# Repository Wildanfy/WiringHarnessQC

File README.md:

**README.md**

---

## QC Cable Tester Berbasis ESP32 + Bluetooth

**Deskripsi Singkat**
Proyek ini adalah implementasi sistem Quality Control (QC) untuk pengujian konektivitas kabel, menggunakan modul ESP32, rangkaian shift register 80/88-bit, multiplexer (MUX) hingga 6 buah, dan koneksi Bluetooth. Dengan satu rangkaian, Anda dapat memeriksa hingga 76 kanal “normal” dan 8 kanal “X” secara otomatis. Hasil QC (terhubung, putus, short, salah jalur) kemudian dikirim melalui USB Serial dan Bluetooth Serial secara bersamaan dalam format teks.

---

## Daftar Isi

1. [Fitur Utama](#fitur-utama)
2. [Persyaratan Hardware](#persyaratan-hardware)
3. [Skema Pin dan Konektivitas](#skema-pin-dan-konektivitas)
4. [Persiapan Perangkat Lunak](#persiapan-perangkat-lunak)
5. [Cara Mengunggah (Upload) ke ESP32](#cara-mengunggah-upload-ke-esp32)
6. [Perintah Bluetooth / USB Serial](#perintah-bluetooth--usb-serial)
7. [Penjelasan Fungsi-Fungsi Utama](#penjelasan-fungsi-fungsi-utama)
8. [Format Output QC](#format-output-qc)

---

## Fitur Utama

* **Pengujian 76 Kanal Normal**

  * Memanfaatkan 5 buah MUX 16:1 untuk membaca kondisi setiap pin kabel di kanal 1–76.
  * Deteksi otomatis:

    * `C` (Connected)
    * `N` (Disconnected)
    * `S&<nomor partner>` (Short dengan kanal lain)
    * `W&<nomor partner>` (Miswire / salah jalur)
  * Penanganan kondisi khusus (edge-case) pada grup K2 dan K3 sesuai skema QC kabel di dokumentasi.
* **Pengujian 8 Kanal “X” (MUX6)**

  * Rangkaian tambahan untuk kabel tipe “X” (kanal 80–87) menggunakan MUX6.
  * Deteksi antar-MUX: apabila kanal X terhubung / short / miswire ke salah satu dari 88 global bit (76 kanal normal + 8 X).
* **Bluetooth Serial + USB Serial**

  * Nama perangkat Bluetooth: **“QC Cable”**
  * Hasil pengukuran QC langsung dikirim ke kedua antarmuka (Serial USB & Bluetooth).
  * Komunikasi satu arah (ESP32 → PC / Handphone) untuk log hasil QC.
* **Mode QC Fleksibel**

  * `start` : hanya QC kabel normal (1–76)
  * `startx`: hanya QC kabel X (80–87)
  * `startall`: QC semua secara bersamaan (1–76 dan 80–87)
  * `stop` : menghentikan pengukuran QC dan mereset pin

---

## Persyaratan Hardware

1. **ESP32** (atau varian serupa dengan fitur BluetoothClassic)
2. **Shift Register 80-bit / 88-bit**

   * Anda dapat menyusun rangkaian shift register (misalnya menggunakan beberapa IC 74HC595 beruntun) untuk total 80 bit.
   * Untuk skema kabel “X” (8 kanal tambahan), gunakan shift register hingga 88 bit.
3. **Multiplexer (MUX)**

   * 5 buah MUX 16:1 (misal CD74HC4067 atau sejenis). Masing-masing MUX menangani 16 bit sinyal dari shift register untuk 76 kanal normal (5×16 = 80, gunakan 76).
   * 1 buah MUX 16:1 untuk kabel “X” (kanal 80–87).
4. **Kabel Jumper / Breadboard**
5. **Catu Daya 5V (untuk MUX & Shift Register)**
6. **Kabel Uji / Fixture**

   * Sambungkan kabel-kabel yang akan diuji ke pin output shift register / MUX sesuai diagram.
7. **Komputer / Smartphone**

   * Untuk menerima data QC via USB Serial atau Bluetooth Serial.

---

## Skema Pin dan Konektivitas

```
ESP32                              Shift Register / MUX / Fixture
--------------------------------------------------------------------------------
GPIO 23   (DS)      → Data (SER) pada shift register
GPIO 18   (SHCP)    → Clock (SRCLK) pada shift register
GPIO 5    (STCP)    → Latch (RCLK) pada shift register

GPIO 26   (SIG)     ← Output “sense” (hasil pembacaan) dari MUX (digitalRead)
GPIO 13   (S0)      → Select bit 0 pada semua MUX (S0)
GPIO 12   (S1)      → Select bit 1 pada semua MUX (S1)
GPIO 14   (S2)      → Select bit 2 pada semua MUX (S2)
GPIO 19   (S3)      → Select bit 3 pada semua MUX (S3)

GPIO 25   (EN_MUX1) → Enable MUX1 (untuk kanal 1–16)
GPIO 33   (EN_MUX2) → Enable MUX2 (untuk kanal 17–32)
GPIO 15   (EN_MUX3) → Enable MUX3 (untuk kanal 33–48)
GPIO 2    (EN_MUX4) → Enable MUX4 (untuk kanal 49–64)
GPIO 4    (EN_MUX5) → Enable MUX5 (untuk kanal 65–80)

GPIO 27   (EN_MUX6) → Enable MUX6 (untuk kabel X, kanal 80–87)
```

* **Catatan Channel Mapping**

  * Kanall 1–13 → `K1-A1` … `K1-A13`
  * Kanall 14–26 → `K1-B1` … `K1-B13`
  * Kanall 27–39 → `K2-A1` … `K2-A13`
  * Kanall 40–52 → `K2-B1` … `K2-B13`
  * Kanall 53–64 → `K3-A1` … `K3-A12`
  * Kanall 65–76 → `K3-B1` … `K3-B12`
  * Kabel “X” (8 kanal) → `X-1` … `X-8`

---

## Persiapan Perangkat Lunak

1. **Install Arduino IDE (versi terbaru disarankan)**

   * Bisa diunduh di [https://www.arduino.cc/en/software](https://www.arduino.cc/en/software) (sesuaikan OS)
2. **Tambahkan Board ESP32 ke Arduino IDE**

   * Buka **File → Preferences**
   * Tambahkan URL berikut ke `Additional Boards Manager URLs`:

     ```
     https://raw.githubusercontent.com/espressif/arduino-esp32/gh-pages/package_esp32_index.json
     ```
   * Buka **Tools → Board → Boards Manager**, cari “esp32” lalu install “esp32 by Espressif Systems”.
3. **Library yang Diperlukan**

   * `BluetoothSerial.h` (sudah tersedia saat menginstal board ESP32)
   * Tidak ada library eksternal lain (semua fungsi shift register dan multiplexer ditulis manual).

---

## Cara Mengunggah (Upload) ke ESP32

1. Sambungkan ESP32 ke komputer via kabel USB.
2. Pastikan di **Tools → Board** sudah terbaca **“ESP32 Dev Module”** (atau tipe ESP32 yang Anda gunakan).
3. Pilih **Port** yang sesuai (Tools → Port).
4. Buka file `QC_Cable.ino` (atau ganti nama menjadi `QC_Cable.ino`) pada Arduino IDE.
5. Tekan tombol **Upload** (ikon panah kanan). Tunggu hingga proses selesai, ESP32 otomatis restart.

---

## Perintah Bluetooth / USB Serial

Setelah kode berhasil berjalan, ESP32 akan menunggu perintah via USB Serial (baud rate 115200) ataupun Bluetooth Serial (“QC Cable”).
Ketik salah satu perintah berikut (tanpa tanda kutip) lalu tekan **Enter**:

* `start`

  * Menjalankan QC hanya untuk **kanal normal** (1–76).
* `startx`

  * Menjalankan QC hanya untuk **kanal “X”** (80–87).
* `startall`

  * Menjalankan QC untuk **semua kanal** (1–76 dan 80–87).
* `stop`

  * Menghentikan QC, mereset pin, dan berhenti mengirim data.

**Contoh penggunaan di Serial Monitor:**

```
> startall
```

ESP32 akan mengirimkan hasil QC berulang setiap interval 10 ms ke Serial/BT.

---

## Penjelasan Fungsi-Fungsi Utama

1. **`resetPins()`**

   * Mengatur semua pin ESP32 (DS, SHCP, STCP, SIG, S0–S3, EN\_MUX1–EN\_MUX6) ke `OUTPUT` atau `INPUT_PULLDOWN` sesuai fungsinya.
   * Memastikan initial state: latch low, clock low, data low, MUX6 (EN\_MUX6) di-`HIGH` (non-aktif).

2. **`shiftOut80(uint64_t data)`**

   * Mengirim 76 bit (dipadatkan menjadi 80 bit) ke rangkaian shift register secara paling signifikan (MSB) terlebih dahulu.
   * `data` berupa `uint64_t` dimana bit ke-0 (LSB) → kanal terakhir (nomor 75).

3. **`readMux16(int muxNumber)`**

   * Membaca 16 bit data dari MUX tertentu (1–5) dengan mengaktifkan satu `EN_MUXx` pada `LOW` dan membaca pin SIG pada setiap kombinasi `S0–S3`.
   * Mengembalikan `uint16_t` yang menandakan status HIGH/LOW pada 16 output MUX.

4. **`readAllMux(bool globalMap[], int maxCh)`**

   * Membaca MUX1–5 sekaligus, memasukkan hasilnya ke array `globalMap[]` (panjang minimal `maxCh`).
   * Hanya mengisi hingga indeks `maxCh−1`.

5. **`runQC_K1(String &outputBuffer)`**, **`runQC_K2(...)`**, **`runQC_K3(...)`**

   * Masing-masing menangani QC pada grup kabel:

     * **K1** = kanal global 0–25 (K1-A1..K1-A13, K1-B1..K1-B13)
     * **K2** = kanal global 26–51 (K2-A1..K2-A13, K2-B1..K2-B13)
     * **K3** = kanal global 52–75 (K3-A1..K3-A12, K3-B1..K3-B12)
   * Setiap fungsi:

     1. **Inisialisasi** array `ChannelResult results[...]` (state & partner).
     2. Untuk tiap channel `ch` di kelompoknya:

        * Jika `channelUsed[ch]` = `false`, tandai state = −1 (skip).
        * Lakukan `shiftOut80(1ULL << ch)`, delay, `readAllMux(...)` ke `globalMap[]`.
        * Hitung `totalActive` dalam kelompok tersebut.
        * Tentukan `state` (CONNECTED, SHORT, MISWIRE, DISCONNECTED) dan `partner` (jika SHORT/MISWIRE).
        * Penanganan **kondisi khusus**:

          * **K2**

            * Jika B2 (index internal 10) short ke B13 (index internal 25), dan B13 dianggap putus, tandai kedua channel sebagai CONNECTED.
          * **K3**

            * Jika A5 (index internal 4) putus, dan B1 (index internal 12) short ke A5, tandai keduanya sebagai CONNECTED.
     3. **Cetak hasil**: untuk tiap channel, bentuk string `"Label:State,"` (contoh: `K1-A1:C,` atau `K2-B5:W&B12,`). Tambahkan ke `outputBuffer`.

6. **`shiftOut88(uint8_t data[11])`**

   * Serupa `shiftOut80`, tetapi menggunakan array 11 byte untuk total 88 bit (1 bit extra).

7. **`readMux16X()`**

   * Membaca MUX6 (kanal X) dengan mengaktifkan `EN_MUX6 = LOW` dan membaca 16 bit, meski kanal X hanya 8 bit (bit 0–7).

8. **`runQCX(String &outputBuffer)`**

   * Menangani QC untuk 8 kanal X (global bit 80–87).
   * Algoritmanya mirip `runQC_K*`, tetapi mencakup pembacaan **seluruh 88 bit** (MUX1–5 + MUX6) untuk deteksi antar-MUX.
   * Hasil (“X-1\:C,” atau “X-3\:S\&K2-A5,” dst.) ditambahkan ke `outputBuffer`.

9. **`setup()`**

   * Inisialisasi pin dan `Serial.begin(115200)`, `SerialBT.begin("QC Cable")`.
   * `delay(1000)` singkat agar Bluetooth siap.

10. **`loop()`**

    * Terus-menerus:

      * Baca karakter dari `Serial` (USB) & `SerialBT` (Bluetooth), kumpulkan ke `bufUSB` / `bufBT`.
      * Jika ditemukan substring:

        * `"startall"`, `"startx"`, `"start"`, `"stop"` → setel `qcRunning`, `qcActive`, `qcActiveX`, `qcAllActive` sesuai mode.
      * Jika `qcRunning == true` dan interval (10 ms) tercapai:

        * Panggil `runQC_K1()`, `runQC_K2()`, `runQC_K3()` apabila mode `qcActive`/`qcAllActive`.
        * Panggil `runQCX()` apabila mode `qcActiveX`/`qcAllActive`.
        * Kirim `out` (`String` hasil QC) melalui `Serial.println(out)` dan `SerialBT.println(out)`.

---

## Format Output QC

Hasil QC dikomunikasikan dalam satu baris teks, misalnya:

```
K1-A1:C,K1-A2:N,K1-A3:S&K1-B5,...,K3-B12:W&K3-A8,X-1:C,X-2:N,X-3:S&K2-B4,...
```

* **Format umum per-kanal:**

  ```
  <Label>:<State>[&<LabelPartner>],
  ```

  * `<Label>`

    * Contoh: `K1-A1`, `K2-B7`, `K3-A12`, `X-5`
  * `<State>`

    * `C` = Connected (terhubung sempurna satu-ke-satu)
    * `N` = Disconnected (putus, tidak terdeteksi sama sekali)
    * `S&<LabelPartner>` = Short (terhubung dengan lebih dari satu bit; partner ditunjukkan)
    * `W&<LabelPartner>` = Miswire (sinyal keluar dari kelompok yang diharapkan)
  * `<LabelPartner>`

    * Menunjukkan label kanal lain yang terhubung / short / miswire. Pada `S&`/`W&`, `LabelPartner` hanya substring setelah tanda “-” (misal `B5`, `A12`).

**Contoh Lengkap**

```
K1-A1:C,K1-A2:N,K1-A3:S&K1-B5,K1-A4:W&K2-A1,...,K3-B12:C,X-1:N,X-2:C,X-3:S&K1-A7,...
```

---

### Catatan Tambahan

* Pastikan bahwa **`channelUsed[]`** diinisialisasi sesuai kebutuhan. Nilai `false` akan menyebabkan pemrosesan kanal tersebut di-skip. Anda dapat menonaktifkan atau mengaktifkan kanal tertentu dengan mengubah array `channelUsed[76]` pada baris awal kode.
* Jika Anda ingin menyesuaikan interval QC (delay antara iterasi), ubah konstanta `const unsigned long qcInterval = 10;` (nilai dalam milidetik).
* Penanganan edge-case untuk K2 dan K3 ditujukan untuk kondisi khusus kabel tertentu (misal susunan “B2 short ke B13” atau “A5 disconnected & B1 short ke A5”). Silakan sesuaikan logika ini jika topologi kabel Anda berbeda.

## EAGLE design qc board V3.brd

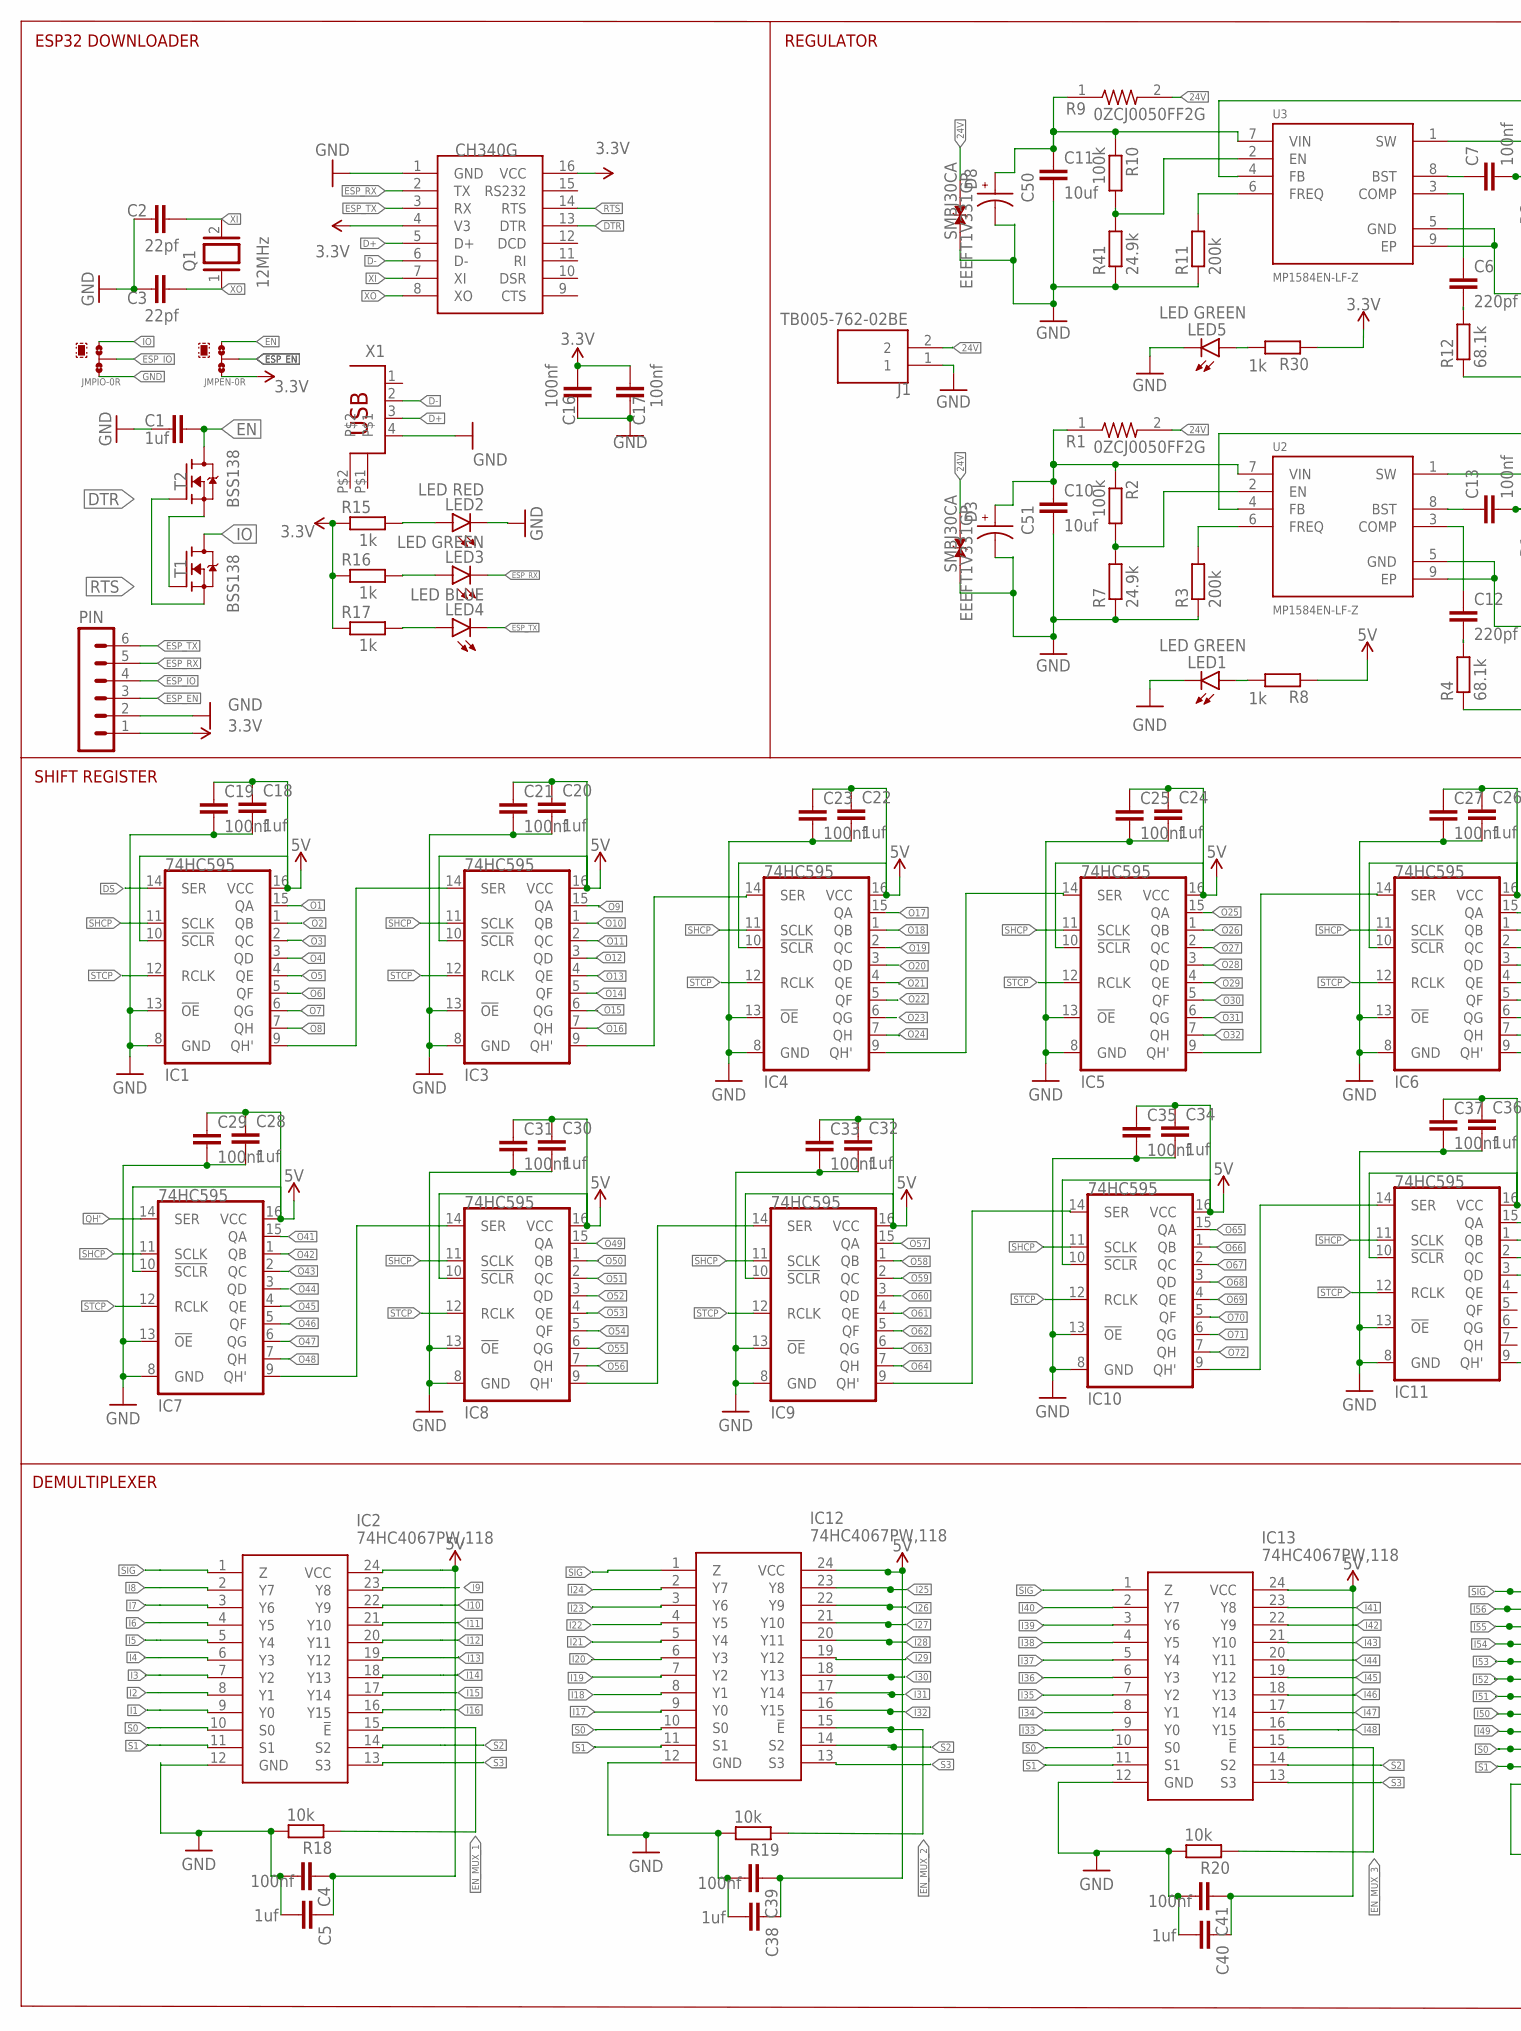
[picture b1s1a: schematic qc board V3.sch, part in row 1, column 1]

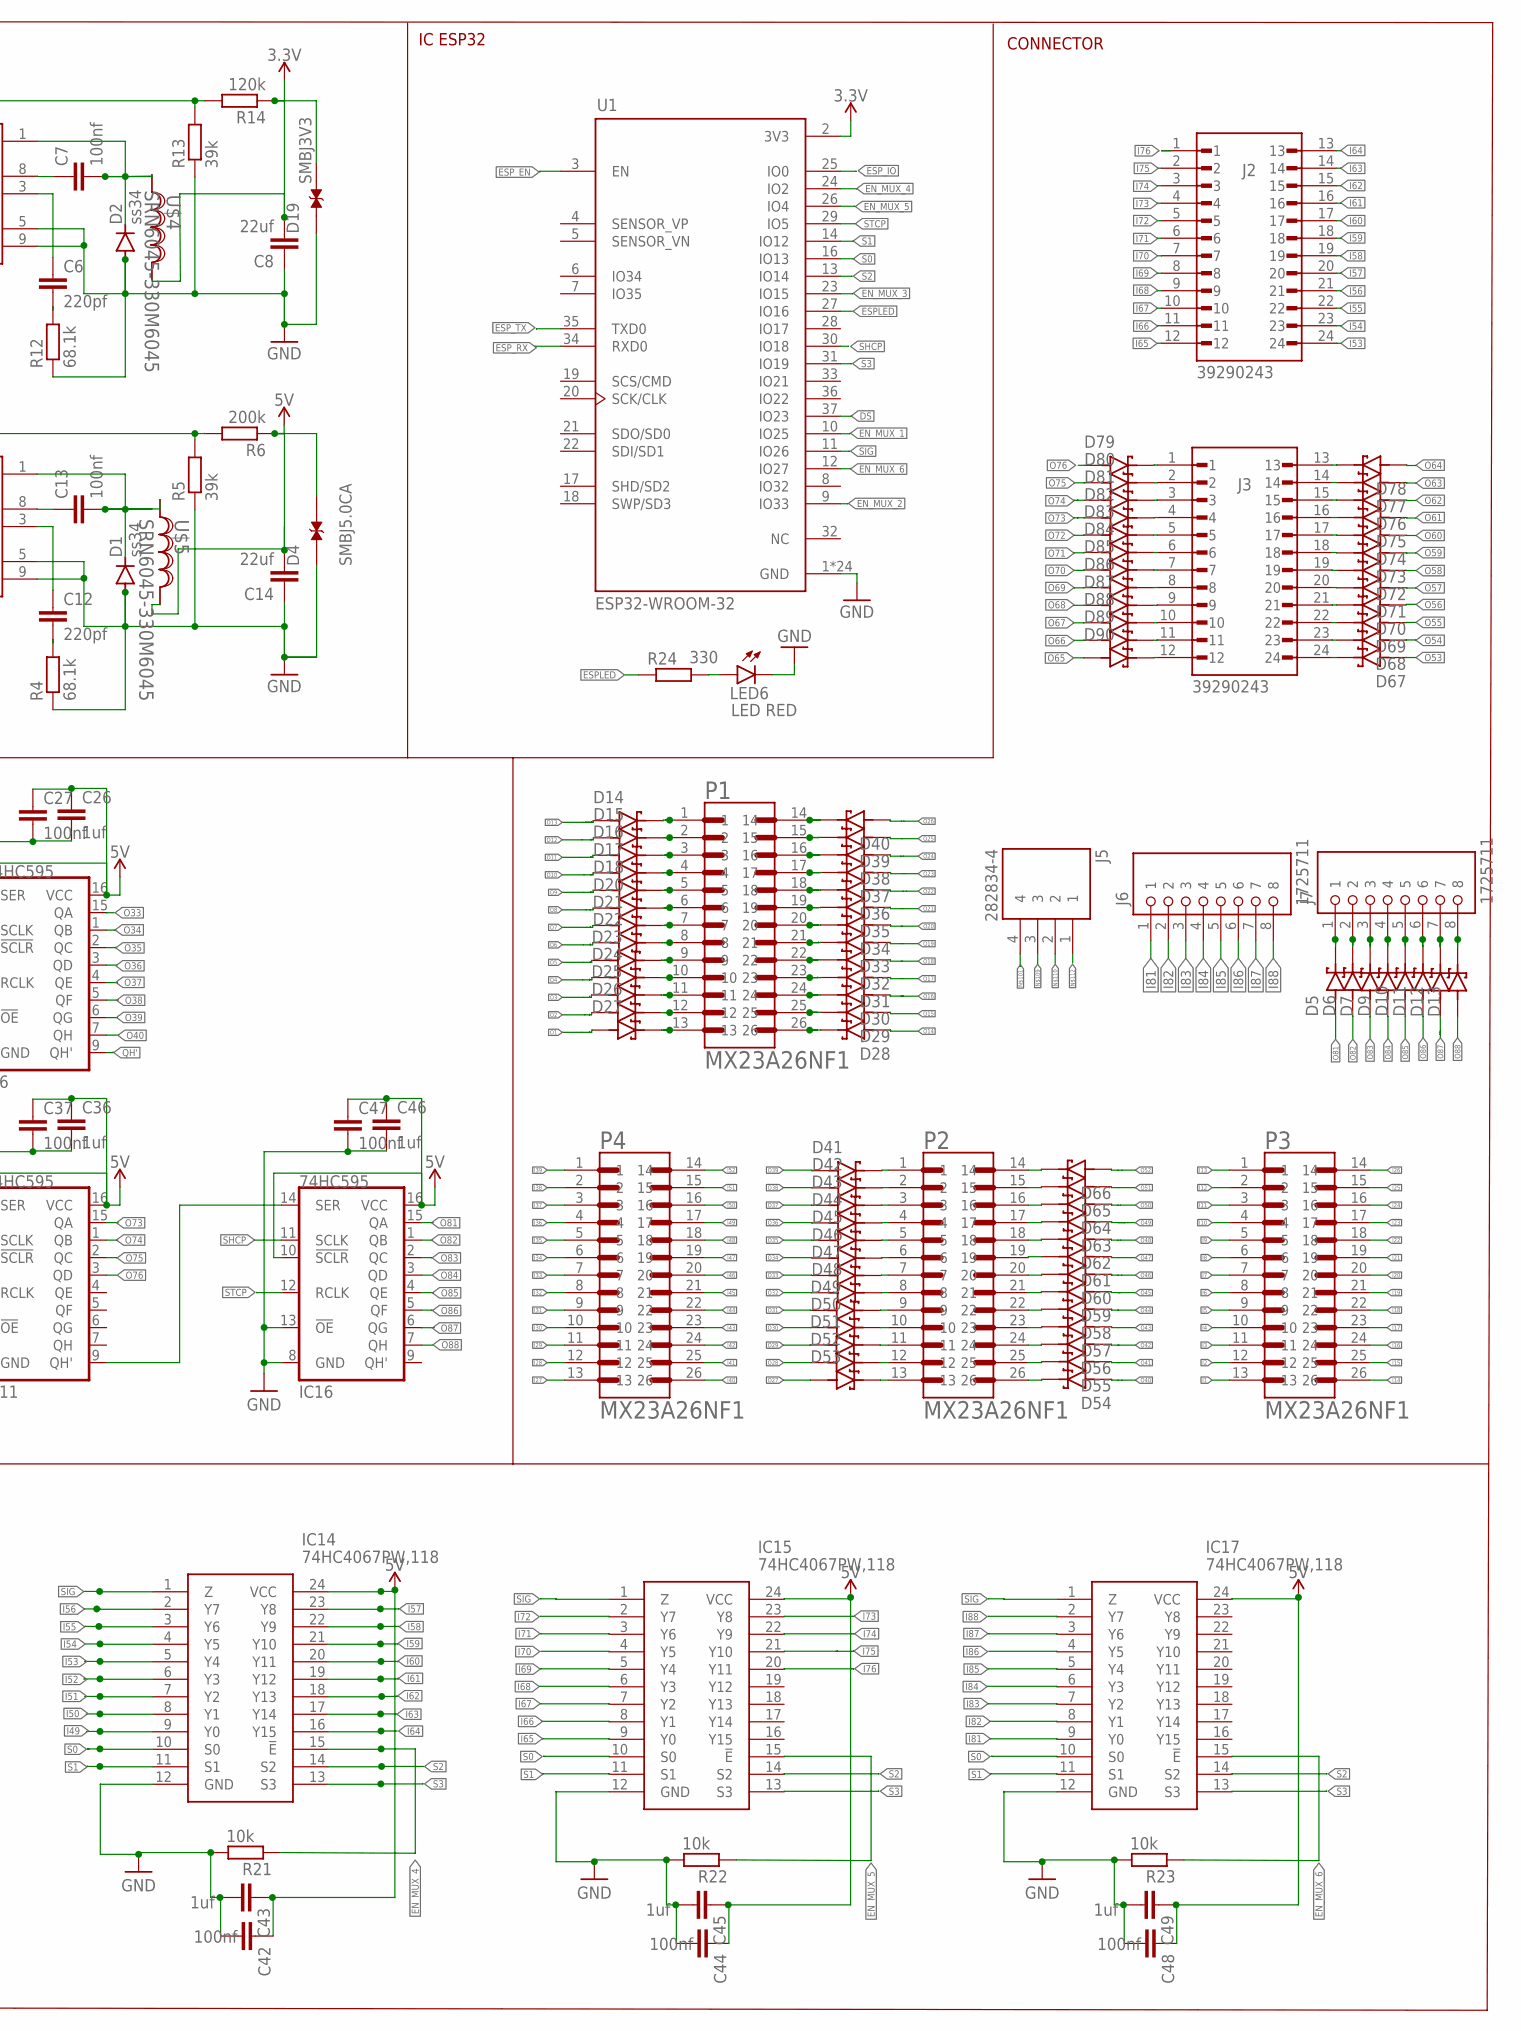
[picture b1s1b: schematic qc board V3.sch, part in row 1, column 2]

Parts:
C1, C5, C18, C20, C22, C24, C26, C28, C30, C32, C34, C36, C38, C40, C43, C45, C46, C49: 1uf; C0805
C2, C3: 22pf; C0805
C4, C7, C13, C16, C17, C19, C21, C23, C25, C27, C29, C31, C33, C35, C37, C39, C41, C42, C44, C47, C48: 100nf; C0805
C6, C12: 220pf; C0805
C8, C14: 22uf; C0805
C10, C11: 10uf; C0805
C50, C51: EEEFT1V331GP; CAP_EEEFT1V331GP
D1, D2: ss34; SMB
D3, D8: SMBJ30CA; DIOM4336X265N
D4: SMBJ5.0CA; DIOM4336X265N
D5, D6, D7, D9, D10, D11, D12, D13, D14, D15, D16, D17, D18, D20, D21, D22, D23, D24, D25, D26, D27, D28, D29, D30, D31, D32, D33, D34, D35, D36, D37, D38, D39, D40, D41, D42, D43, D44, D45, D46, D47, D48, D49, D50, D51, D52, D53, D54, D55, D56, D57, D58, D59, D60, D61, D62, D63, D64, D65, D66, D67, D68, D69, D70, D71, D72, D73, D74, D75, D76, D77, D78, D79, D80, D81, D82, D83, D84, D85, D86, D87, D88, D89, D90: 1N5819HW-7; SOD3715X145N
D19: SMBJ3V3; DIOM4336X265N
IC1, IC3, IC4, IC5, IC6, IC7, IC8, IC9, IC10, IC11, IC16: 74HC595; SO16
IC2, IC12, IC13, IC14, IC15, IC17: 74HC4067PW,118; SOP65P640X110-24N
J1: TB005-762-02BE; CUI_TB005-762-02BE
J2, J3: 39290243; MOLEX_39290243
J5: 282834-4; TE_282834-4
J6, J7: 1725711; PHOENIX_1725711
JMPEN: 0R-JUMPB; B0R-JMP
JMPIO: 0R-JUMPB; B0R-JMP
LED1, LED5: LED GREEN; CHIP-LED0805
LED2: LED RED; CHIPLED_0805
LED3: LED GREEN; CHIPLED_0805
LED4: LED BLUE; CHIPLED_0805
LED6: LED RED; CHIP-LED0805
P1, P2, P3, P4: MX23A26NF1; JAE_MX23A26NF1
PIN: MA06-1
Q1: 12MHz; QS
R1, R9: 0ZCJ0050FF2G; RESC3216X125N
R2, R10: 100k; R0805
R3, R6, R11: 200k; R0805
R4, R12: 68.1k; R0805
R5, R13: 39k; R0805
R7, R41: 24.9k; R0805
R8, R30: 1k; R0805
R14: 120k; R0805
R15, R16, R17: 1k; M0805
R18, R19, R20, R21, R22, R23: 10k; M0805
R24: 330; R0805
T1, T2: BSS138; SOT95P240X111-3N
U1: ESP32-WROOM-32; MODULE_ESP32-WROOM-32
U2, U3: MP1584EN-LF-Z; SOIC127P600X170-9N
U$3: CH340G; SOIC16
U$4, U$5: SRN6045-330M6045; SRN6045
X1: PN61729

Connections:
3.3V: C8.2, C16.1, C17.1, D19.2, JMPEN.3, PIN.1, R14.1, R15.1, R16.1, R17.1, R30.1, U1.2 (3V3), U$3.4 (V3), U$3.16 (VCC), U$4.1
5V: C4.1, C5.1, C14.2, C18.1, C19.1, C20.1, C21.1, C22.1, C23.1, C24.1, C25.1, C26.1, C27.1, C28.1, C29.1, C30.1, C31.1, C32.1, C33.1, C34.1, C35.1, C36.1, C37.1, C38.1, C39.1, C40.1, C41.1, C42.1, C43.1, C44.1, C45.1, C46.1, C47.1, C48.1, C49.1, D4.2, IC1.10 (!SCLR), IC1.16 (VCC), IC2.24 (VCC), IC3.10 (!SCLR), IC3.16 (VCC), IC4.10 (!SCLR), IC4.16 (VCC), IC5.10 (!SCLR), IC5.16 (VCC), IC6.10 (!SCLR), IC6.16 (VCC), IC7.10 (!SCLR), IC7.16 (VCC), IC8.10 (!SCLR), IC8.16 (VCC), IC9.10 (!SCLR), IC9.16 (VCC), IC10.10 (!SCLR), IC10.16 (VCC), IC11.10 (!SCLR), IC11.16 (VCC), IC12.24 (VCC), IC13.24 (VCC), IC14.24 (VCC), IC15.24 (VCC), IC16.10 (!SCLR), IC16.16 (VCC), IC17.24 (VCC), R6.1, R8.1, U$5.1
24V: D3.1, D8.1, J1.2, R1.2, R9.2
D+: U$3.5 (D+), X1.3
D-: U$3.6 (D-), X1.2
DS: IC1.14 (SER), U1.37 (IO23)
DTR: T1.2 (S), T2.1 (G), U$3.13 (DTR)
EN: C1.1, JMPEN.1, T2.3 (D)
EN_MUX_1: IC2.15 (!E), R18.1, U1.10 (IO25)
EN_MUX_2: IC12.15 (!E), R19.1, U1.9 (IO33)
EN_MUX_3: IC13.15 (!E), R20.1, U1.23 (IO15)
EN_MUX_4: IC14.15 (!E), R21.1, U1.24 (IO2)
EN_MUX_5: IC15.15 (!E), R22.1, U1.26 (IO4)
EN_MUX_6: IC17.15 (!E), R23.1, U1.12 (IO27)
ESPLED: R24.1, U1.27 (IO16)
ESP_EN: JMPEN.2, PIN.3, U1.3 (EN)
ESP_IO: JMPIO.2, PIN.4, U1.25 (IO0)
ESP_RX: LED3.C, PIN.5, U1.34 (RXD0), U$3.2 (TX)
ESP_TX: LED4.C, PIN.6, U1.35 (TXD0), U$3.3 (RX)
GND: C1.2, C2.2, C3.2, C4.2, C5.2, C8.1, C10.2, C11.2, C14.1, C16.2, C17.2, C18.2, C19.2, C20.2, C21.2, C22.2, C23.2, C24.2, C25.2, C26.2, C27.2, C28.2, C29.2, C30.2, C31.2, C32.2, C33.2, C34.2, C35.2, C36.2, C37.2, C38.2, C39.2, C40.2, C41.2, C42.2, C43.2, C44.2, C45.2, C46.2, C47.2, C48.2, C49.2, C50.2, C51.2, D1.A, D2.A, D3.2, D4.1, D8.2, D19.1, IC1.8 (GND), IC1.13 (!OE), IC2.12 (GND), IC3.8 (GND), IC3.13 (!OE), IC4.8 (GND), IC4.13 (!OE), IC5.8 (GND), IC5.13 (!OE), IC6.8 (GND), IC6.13 (!OE), IC7.8 (GND), IC7.13 (!OE), IC8.8 (GND), IC8.13 (!OE), IC9.8 (GND), IC9.13 (!OE), IC10.8 (GND), IC10.13 (!OE), IC11.8 (GND), IC11.13 (!OE), IC12.12 (GND), IC13.12 (GND), IC14.12 (GND), IC15.12 (GND), IC16.8 (GND), IC16.13 (!OE), IC17.12 (GND), J1.1, JMPIO.3, LED1.C, LED2.C, LED5.C, LED6.C, PIN.2, R3.1, R4.1, R5.1, R7.1, R11.1, R12.1, R13.1, R18.2, R19.2, R20.2, R21.2, R22.2, R23.2, R41.1, U1.1 (GND), U1.15 (GND), U1.38 (GND), U1.39_1 (GND), U1.39_2 (GND), U1.39_3 (GND), U1.39_4 (GND), U1.39_5 (GND), U1.39_6 (GND), U1.39_7 (GND), U1.39_8 (GND), U1.39_9 (GND), U1.39_10 (GND), U1.39_11 (GND), U1.39_12 (GND), U1.39_13 (GND), U1.39_14 (GND), U1.39_15 (GND), U1.39_16 (GND), U1.39_17 (GND), U1.39_18 (GND), U1.39_19 (GND), U1.39_20 (GND), U1.39_21 (GND), U2.5 (GND), U2.9 (EP), U3.5 (GND), U3.9 (EP), U$3.1 (GND), X1.4
I1: IC2.9 (Y0), P3.13
I2: IC2.8 (Y1), P3.12
I3: IC2.7 (Y2), P3.11
I4: IC2.6 (Y3), P3.10
I5: IC2.5 (Y4), P3.9
I6: IC2.4 (Y5), P3.8
I7: IC2.3 (Y6), P3.7
I8: IC2.2 (Y7), P3.6
I9: IC2.23 (Y8), P3.5
I10: IC2.22 (Y9), P3.4
I11: IC2.21 (Y10), P3.3
I12: IC2.20 (Y11), P3.2
I13: IC2.19 (Y12), P3.1
I14: IC2.18 (Y13), P3.26
I15: IC2.17 (Y14), P3.25
I16: IC2.16 (Y15), P3.24
I17: IC12.9 (Y0), P3.23
I18: IC12.8 (Y1), P3.22
I19: IC12.7 (Y2), P3.21
I20: IC12.6 (Y3), P3.20
I21: IC12.5 (Y4), P3.19
I22: IC12.4 (Y5), P3.18
I23: IC12.3 (Y6), P3.17
I24: IC12.2 (Y7), P3.16
I25: IC12.23 (Y8), P3.15
I26: IC12.22 (Y9), P3.14
I27: IC12.21 (Y10), P4.13
I28: IC12.20 (Y11), P4.12
I29: IC12.19 (Y12), P4.11
I30: IC12.18 (Y13), P4.10
I31: IC12.17 (Y14), P4.9
I32: IC12.16 (Y15), P4.8
I33: IC13.9 (Y0), P4.7
I34: IC13.8 (Y1), P4.6
I35: IC13.7 (Y2), P4.5
I36: IC13.6 (Y3), P4.4
I37: IC13.5 (Y4), P4.3
I38: IC13.4 (Y5), P4.2
I39: IC13.3 (Y6), P4.1
I40: IC13.2 (Y7), P4.26
I41: IC13.23 (Y8), P4.25
I42: IC13.22 (Y9), P4.24
I43: IC13.21 (Y10), P4.23
I44: IC13.20 (Y11), P4.22
I45: IC13.19 (Y12), P4.21
I46: IC13.18 (Y13), P4.20
I47: IC13.17 (Y14), P4.19
I48: IC13.16 (Y15), P4.18
I49: IC14.9 (Y0), P4.17
I50: IC14.8 (Y1), P4.16
I51: IC14.7 (Y2), P4.15
I52: IC14.6 (Y3), P4.14
I53: IC14.5 (Y4), J2.24
I54: IC14.4 (Y5), J2.23
I55: IC14.3 (Y6), J2.22
I56: IC14.2 (Y7), J2.21
I57: IC14.23 (Y8), J2.20
I58: IC14.22 (Y9), J2.19
I59: IC14.21 (Y10), J2.18
I60: IC14.20 (Y11), J2.17
I61: IC14.19 (Y12), J2.16
I62: IC14.18 (Y13), J2.15
I63: IC14.17 (Y14), J2.14
I64: IC14.16 (Y15), J2.13
I65: IC15.9 (Y0), J2.12
I66: IC15.8 (Y1), J2.11
I67: IC15.7 (Y2), J2.10
I68: IC15.6 (Y3), J2.9
I69: IC15.5 (Y4), J2.8
I70: IC15.4 (Y5), J2.7
I71: IC15.3 (Y6), J2.6
I72: IC15.2 (Y7), J2.5
I73: IC15.23 (Y8), J2.4
I74: IC15.22 (Y9), J2.3
I75: IC15.21 (Y10), J2.2
I76: IC15.20 (Y11), J2.1
I81: IC17.9 (Y0), J6.1
I82: IC17.8 (Y1), J6.2
I83: IC17.7 (Y2), J6.3
I84: IC17.6 (Y3), J6.4
I85: IC17.5 (Y4), J6.5
I86: IC17.4 (Y5), J6.6
I87: IC17.3 (Y6), J6.7
I88: IC17.2 (Y7), J6.8
IO: JMPIO.1, T1.3 (D)
unnamed: R10.2, R41.2, U3.2 (EN)
unnamed: R3.2, U2.6 (FREQ)
unnamed: R11.2, U3.6 (FREQ)
unnamed: C7.1, U3.8 (BST)
unnamed: C7.2, D2.C, U3.1 (SW), U$4.2
unnamed: C13.1, U2.8 (BST)
unnamed: C6.2, R12.2
unnamed: C6.1, U3.3 (COMP)
unnamed: LED5.A, R30.2
unnamed: R13.2, R14.2, U3.4 (FB)
unnamed: C13.2, D1.C, U2.1 (SW), U$5.2
unnamed: R5.2, R6.2, U2.4 (FB)
unnamed: C12.2, R4.2
unnamed: R2.2, R7.2, U2.2 (EN)
unnamed: C12.1, U2.3 (COMP)
unnamed: LED1.A, R8.2
unnamed: LED2.A, R15.2
unnamed: LED3.A, R16.2
unnamed: LED4.A, R17.2
unnamed: IC11.9 (QH'), IC16.14 (SER)
unnamed: D5.C (K), J7.1
unnamed: D6.C (K), J7.2
unnamed: D7.C (K), J7.3
unnamed: D9.C (K), J7.4
unnamed: D10.C (K), J7.5
unnamed: D11.C (K), J7.6
unnamed: D12.C (K), J7.7
unnamed: IC1.9 (QH'), IC3.14 (SER)
unnamed: IC3.9 (QH'), IC4.14 (SER)
unnamed: IC4.9 (QH'), IC5.14 (SER)
unnamed: IC5.9 (QH'), IC6.14 (SER)
unnamed: IC7.9 (QH'), IC8.14 (SER)
unnamed: IC8.9 (QH'), IC9.14 (SER)
unnamed: IC9.9 (QH'), IC10.14 (SER)
unnamed: IC10.9 (QH'), IC11.14 (SER)
unnamed: D13.C (K), J7.8
unnamed: D14.C (K), P1.1
unnamed: D15.C (K), P1.2
unnamed: D16.C (K), P1.3
unnamed: D17.C (K), P1.4
unnamed: D18.C (K), P1.5
unnamed: D20.C (K), P1.6
unnamed: D21.C (K), P1.7
unnamed: D22.C (K), P1.8
unnamed: D23.C (K), P1.9
unnamed: D24.C (K), P1.10
unnamed: D25.C (K), P1.11
unnamed: D26.C (K), P1.12
unnamed: D27.C (K), P1.13
unnamed: D40.C (K), P1.14
unnamed: D39.C (K), P1.15
unnamed: D38.C (K), P1.16
unnamed: D37.C (K), P1.17
unnamed: D36.C (K), P1.18
unnamed: D35.C (K), P1.19
unnamed: D34.C (K), P1.20
unnamed: D33.C (K), P1.21
unnamed: D32.C (K), P1.22
unnamed: D31.C (K), P1.23
unnamed: D30.C (K), P1.24
unnamed: D29.C (K), P1.25
unnamed: D28.C (K), P1.26
unnamed: D41.C (K), P2.1
unnamed: D42.C (K), P2.2
unnamed: D43.C (K), P2.3
unnamed: D44.C (K), P2.4
unnamed: D45.C (K), P2.5
unnamed: D46.C (K), P2.6
unnamed: D47.C (K), P2.7
unnamed: D48.C (K), P2.8
unnamed: D49.C (K), P2.9
unnamed: D50.C (K), P2.10
unnamed: D51.C (K), P2.11
unnamed: D52.C (K), P2.12
unnamed: D53.C (K), P2.13
unnamed: D69.C (K), J3.22
unnamed: D68.C (K), J3.23
unnamed: D66.C (K), P2.14
unnamed: D65.C (K), P2.15
unnamed: D64.C (K), P2.16
unnamed: D63.C (K), P2.17
unnamed: D62.C (K), P2.18
unnamed: D61.C (K), P2.19
unnamed: D60.C (K), P2.20
unnamed: D59.C (K), P2.21
unnamed: D58.C (K), P2.22
unnamed: D57.C (K), P2.23
unnamed: D56.C (K), P2.24
unnamed: D55.C (K), P2.25
unnamed: D54.C (K), P2.26
unnamed: D67.C (K), J3.24
unnamed: D70.C (K), J3.21
unnamed: D78.C (K), J3.13
unnamed: D77.C (K), J3.14
unnamed: D76.C (K), J3.15
unnamed: D75.C (K), J3.16
unnamed: D74.C (K), J3.17
unnamed: D73.C (K), J3.18
unnamed: D72.C (K), J3.19, J5.4
unnamed: D71.C (K), J3.20
unnamed: D79.C (K), J3.1
unnamed: D80.C (K), J3.2
unnamed: D81.C (K), J3.3
unnamed: D82.C (K), J3.4
unnamed: D83.C (K), J3.5
unnamed: D84.C (K), J3.6
unnamed: D85.C (K), J3.7, J5.3
unnamed: D86.C (K), J3.8, J5.2
unnamed: D87.C (K), J3.9
unnamed: D88.C (K), J3.10, J5.1
unnamed: D89.C (K), J3.11
unnamed: D90.C (K), J3.12
unnamed: LED6.A, R24.2
O1: D27.A, IC1.15 (QA)
O2: D26.A, IC1.1 (QB)
O3: D25.A, IC1.2 (QC)
O4: D24.A, IC1.3 (QD)
O5: D23.A, IC1.4 (QE)
O6: D22.A, IC1.5 (QF)
O7: D21.A, IC1.6 (QG)
O8: D20.A, IC1.7 (QH)
O9: D18.A, IC3.15 (QA)
O10: D17.A, IC3.1 (QB)
O11: D16.A, IC3.2 (QC)
O12: D15.A, IC3.3 (QD)
O13: D14.A, IC3.4 (QE)
O14: D28.A, IC3.5 (QF)
O15: D29.A, IC3.6 (QG)
O16: D30.A, IC3.7 (QH)
O17: D31.A, IC4.15 (QA)
O18: D32.A, IC4.1 (QB)
O19: D33.A, IC4.2 (QC)
O20: D34.A, IC4.3 (QD)
O21: D35.A, IC4.4 (QE)
O22: D36.A, IC4.5 (QF)
O23: D37.A, IC4.6 (QG)
O24: D38.A, IC4.7 (QH)
O25: D39.A, IC5.15 (QA)
O26: D40.A, IC5.1 (QB)
O27: D53.A, IC5.2 (QC)
O28: D52.A, IC5.3 (QD)
O29: D51.A, IC5.4 (QE)
O30: D50.A, IC5.5 (QF)
O31: D49.A, IC5.6 (QG)
O32: D48.A, IC5.7 (QH)
O33: D47.A, IC6.15 (QA)
O34: D46.A, IC6.1 (QB)
O35: D45.A, IC6.2 (QC)
O36: D44.A, IC6.3 (QD)
O37: D43.A, IC6.4 (QE)
O38: D42.A, IC6.5 (QF)
O39: D41.A, IC6.6 (QG)
O40: D54.A, IC6.7 (QH)
O41: D55.A, IC7.15 (QA)
O42: D56.A, IC7.1 (QB)
O43: D57.A, IC7.2 (QC)
O44: D58.A, IC7.3 (QD)
O45: D59.A, IC7.4 (QE)
O46: D60.A, IC7.5 (QF)
O47: D61.A, IC7.6 (QG)
O48: D62.A, IC7.7 (QH)
O49: D63.A, IC8.15 (QA)
O50: D64.A, IC8.1 (QB)
O51: D65.A, IC8.2 (QC)
O52: D66.A, IC8.3 (QD)
O53: D67.A, IC8.4 (QE)
O54: D68.A, IC8.5 (QF)
O55: D69.A, IC8.6 (QG)
O56: D70.A, IC8.7 (QH)
O57: D71.A, IC9.15 (QA)
O58: D72.A, IC9.1 (QB)
O59: D73.A, IC9.2 (QC)
O60: D74.A, IC9.3 (QD)
O61: D75.A, IC9.4 (QE)
O62: D76.A, IC9.5 (QF)
O63: D77.A, IC9.6 (QG)
O64: D78.A, IC9.7 (QH)
O65: D90.A, IC10.15 (QA)
O66: D89.A, IC10.1 (QB)
O67: D88.A, IC10.2 (QC)
O68: D87.A, IC10.3 (QD)
O69: D86.A, IC10.4 (QE)
O70: D85.A, IC10.5 (QF)
O71: D84.A, IC10.6 (QG)
O72: D83.A, IC10.7 (QH)
O73: D82.A, IC11.15 (QA)
O74: D81.A, IC11.1 (QB)
O75: D80.A, IC11.2 (QC)
O76: D79.A, IC11.3 (QD)
O81: D5.A, IC16.15 (QA)
O82: D6.A, IC16.1 (QB)
O83: D7.A, IC16.2 (QC)
O84: D9.A, IC16.3 (QD)
O85: D10.A, IC16.4 (QE)
O86: D11.A, IC16.5 (QF)
O87: D12.A, IC16.6 (QG)
O88: D13.A, IC16.7 (QH)
OUT_FUSE: C11.1, C50.1, R9.1, R10.1, U3.7 (VIN)
OUT_FUSE1: C10.1, C51.1, R1.1, R2.1, U2.7 (VIN)
QH': IC6.9 (QH'), IC7.14 (SER)
RTS: T1.1 (G), T2.2 (S), U$3.14 (RTS)
S0: IC2.10 (S0), IC12.10 (S0), IC13.10 (S0), IC14.10 (S0), IC15.10 (S0), IC17.10 (S0), U1.16 (IO13)
S1: IC2.11 (S1), IC12.11 (S1), IC13.11 (S1), IC14.11 (S1), IC15.11 (S1), IC17.11 (S1), U1.14 (IO12)
S2: IC2.14 (S2), IC12.14 (S2), IC13.14 (S2), IC14.14 (S2), IC15.14 (S2), IC17.14 (S2), U1.13 (IO14)
S3: IC2.13 (S3), IC12.13 (S3), IC13.13 (S3), IC14.13 (S3), IC15.13 (S3), IC17.13 (S3), U1.31 (IO19)
SHCP: IC1.11 (SCLK), IC3.11 (SCLK), IC4.11 (SCLK), IC5.11 (SCLK), IC6.11 (SCLK), IC7.11 (SCLK), IC8.11 (SCLK), IC9.11 (SCLK), IC10.11 (SCLK), IC11.11 (SCLK), IC16.11 (SCLK), U1.30 (IO18)
SIG: IC2.1 (Z), IC12.1 (Z), IC13.1 (Z), IC14.1 (Z), IC15.1 (Z), IC17.1 (Z), U1.11 (IO26)
STCP: IC1.12 (RCLK), IC3.12 (RCLK), IC4.12 (RCLK), IC5.12 (RCLK), IC6.12 (RCLK), IC7.12 (RCLK), IC8.12 (RCLK), IC9.12 (RCLK), IC10.12 (RCLK), IC11.12 (RCLK), IC16.12 (RCLK), U1.29 (IO5)
XI: C2.1, Q1.2, U$3.7 (XI)
XO: C3.1, Q1.1, U$3.8 (XO)

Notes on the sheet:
ESP32 DOWNLOADER
REGULATOR
IC ESP32
CONNECTOR
SHIFT REGISTER
DEMULTIPLEXER

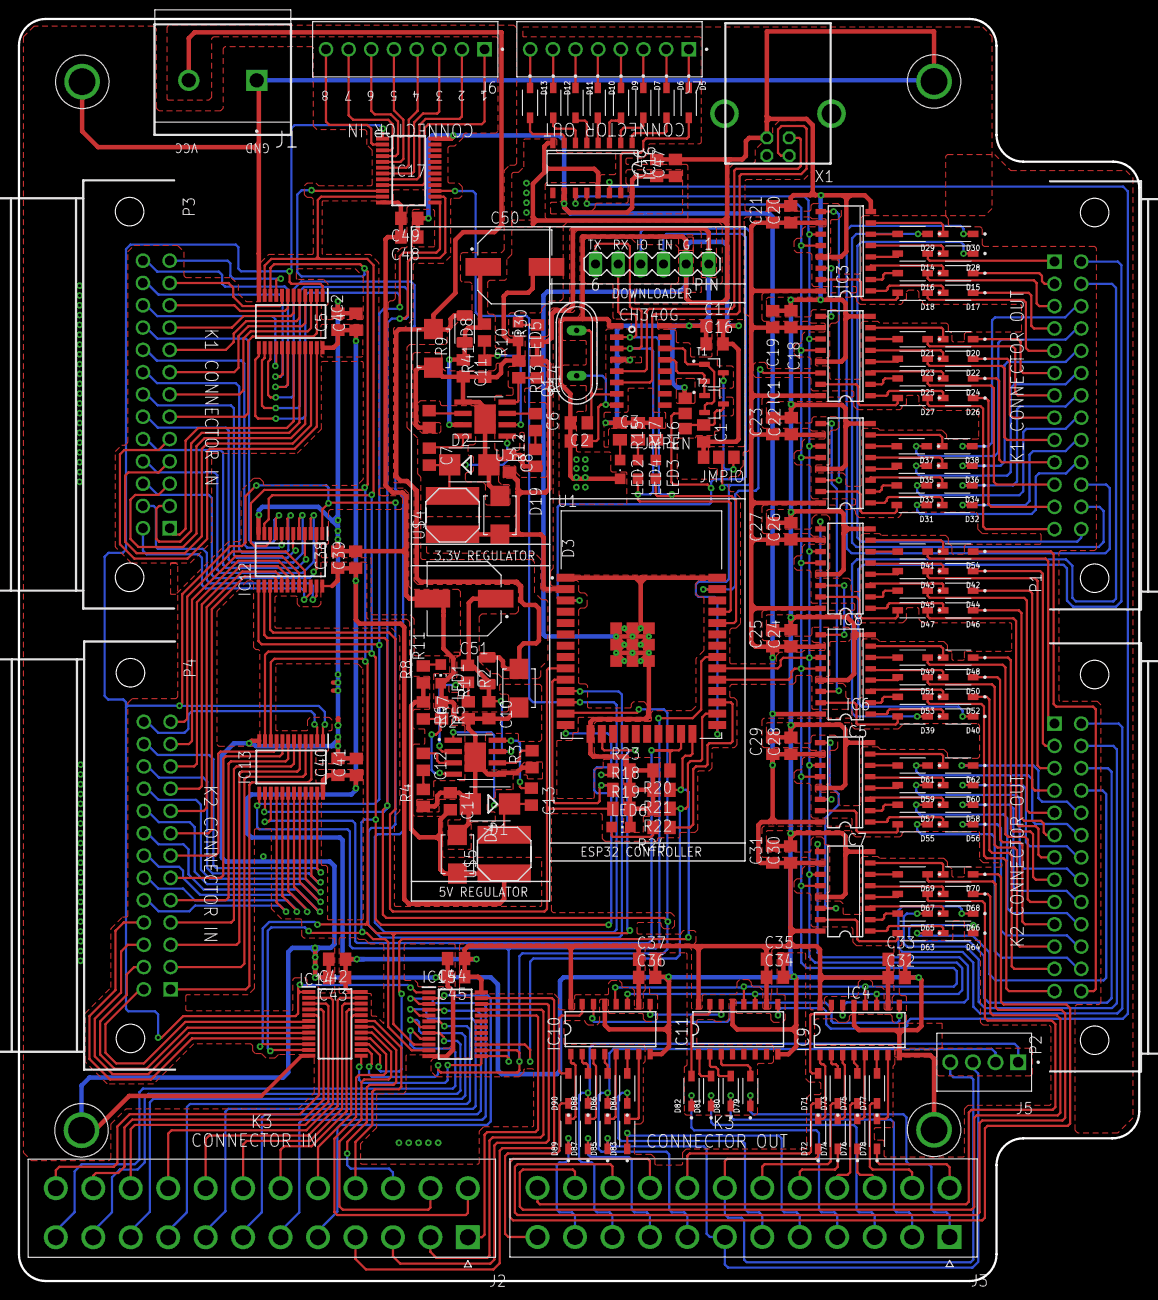
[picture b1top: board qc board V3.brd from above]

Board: 2 copper layers, 125.6 x 141.5 mm, 211 parts (0 on the bottom side), 315 nets.

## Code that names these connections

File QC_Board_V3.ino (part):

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

#define DS 23    // Data (SER)
#define SHCP 18  // Clock (SRCLK)
#define STCP 5   // Latch (RCLK)

#define SIG 26   // Output dari MUX
#define S0 13    // Select pin 0
#define S1 12    // Select pin 1
#define S2 14    // Select pin 2
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
void resetPins() {
  pinMode(DS, OUTPUT);
  pinMode(SHCP, OUTPUT);
  pinMode(STCP, OUTPUT);
  
  digitalWrite(DS, LOW);
  digitalWrite(SHCP, LOW);
  digitalWrite(STCP, LOW);

  pinMode(SIG, INPUT_PULLDOWN);

  pinMode(S0, OUTPUT);
  pinMode(S1, OUTPUT);
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    digitalWrite(S3, (i >> 3) & 0x01);
    delayMicroseconds(10);
    
    pinMode(SIG, INPUT_PULLDOWN);
    int val = digitalRead(SIG);
    if (val == HIGH) {
      muxData |= (1 << i);
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    digitalWrite(S3, (i >> 3) & 0x01);
    delayMicroseconds(10);
    
    pinMode(SIG, INPUT_PULLDOWN);
    int val = digitalRead(SIG);
    if (val == HIGH) {
      muxData |= (1 << i);
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//
void setup() {
  pinMode(DS, OUTPUT);
  pinMode(SHCP, OUTPUT);
  pinMode(STCP, OUTPUT);
  
  pinMode(SIG, INPUT_PULLDOWN);
  
  pinMode(S0, OUTPUT);
  pinMode(S1, OUTPUT);
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

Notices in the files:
parts and their libraries:
SparkFun-PowerSymbols: Licensing: Creative Commons ShareAlike 4.0 International - https://creativecommons.org/licenses/by-sa/4.0
